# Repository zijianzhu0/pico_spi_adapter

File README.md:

# pico_spi_adapter
A rpi pico adapter for asm330lhh.

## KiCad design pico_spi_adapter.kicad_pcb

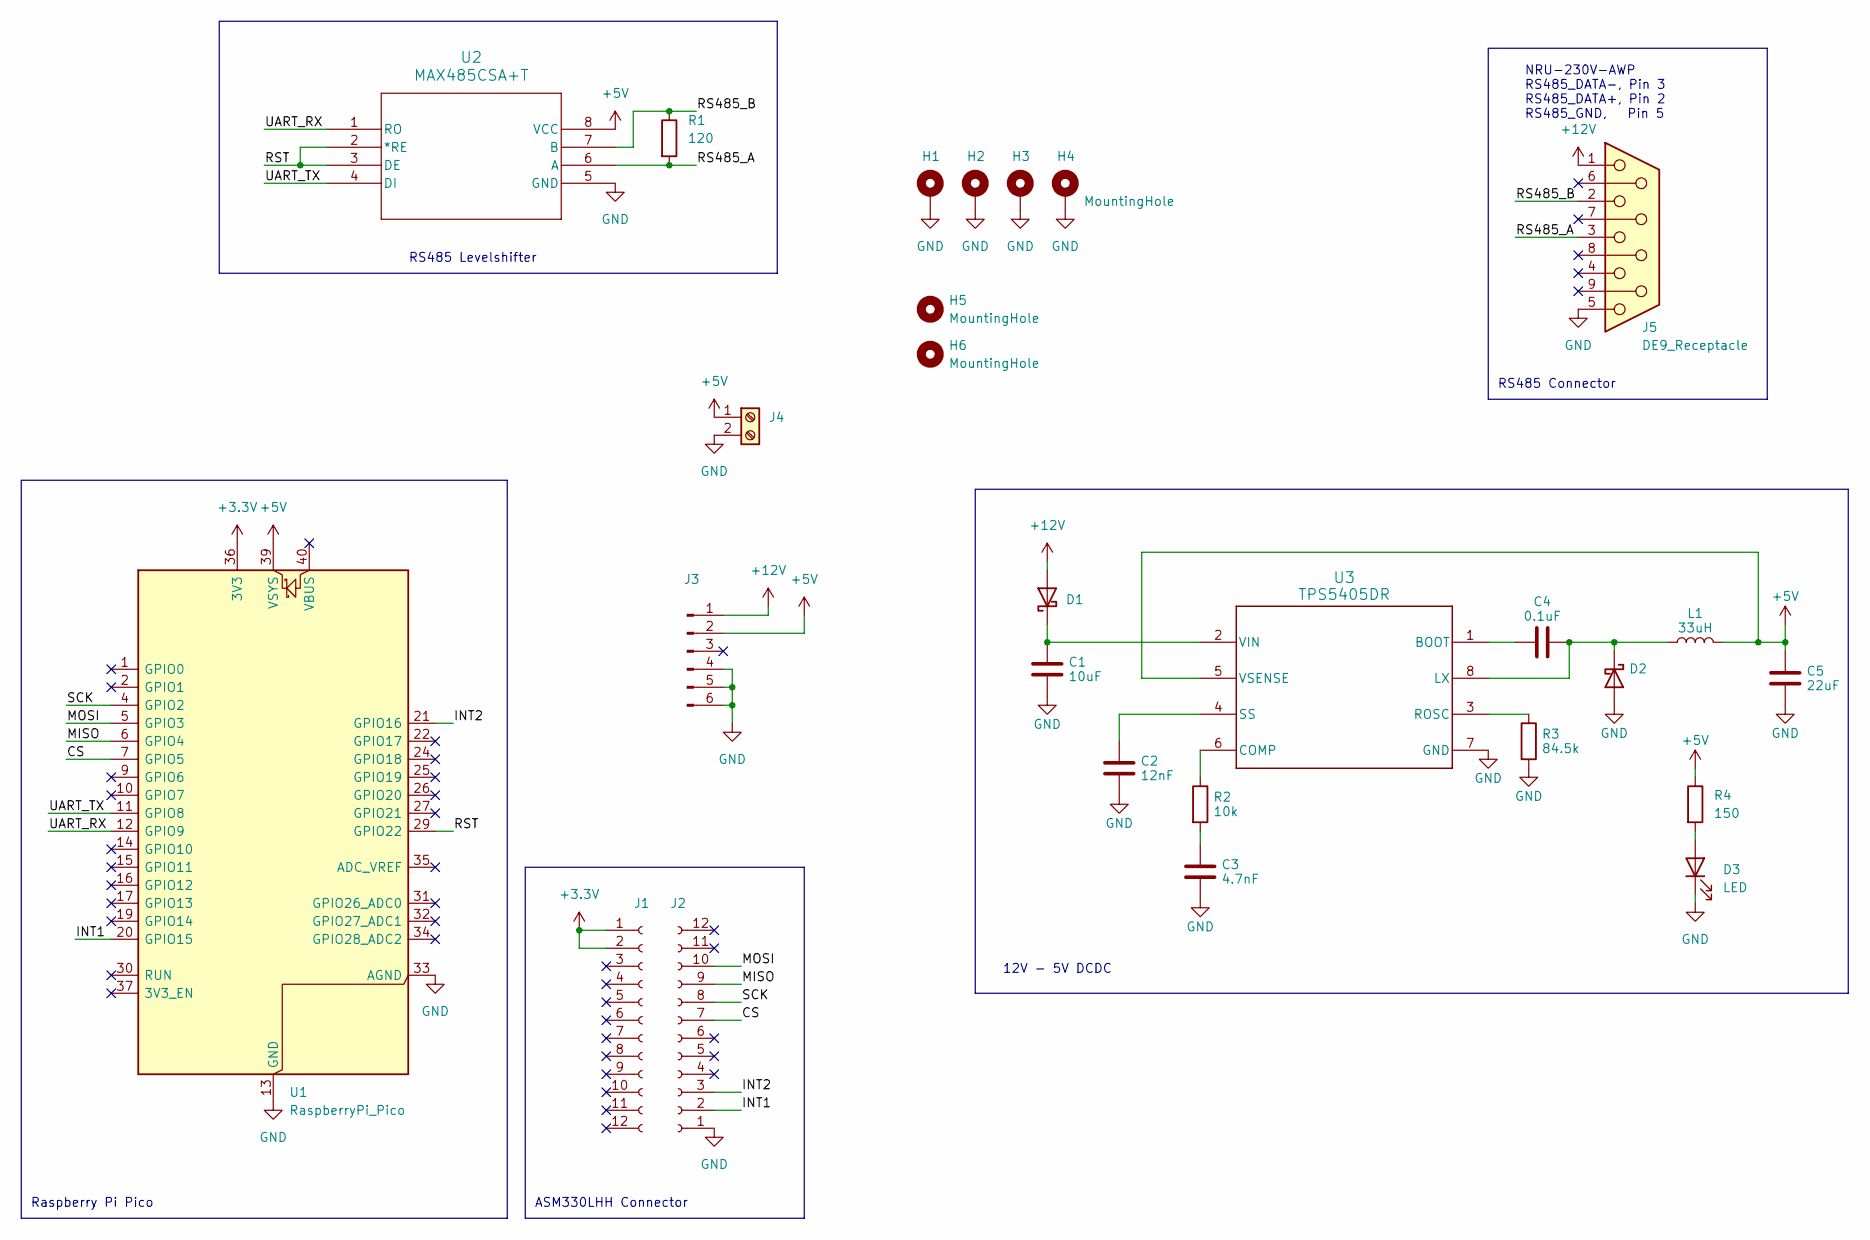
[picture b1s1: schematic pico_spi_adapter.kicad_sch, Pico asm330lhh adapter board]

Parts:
C1: 10uF; C_0805_2012Metric; JLCPCB Part# C15850
C2: 12nF; C_1206_3216Metric; JLCPCB Part# C710999
C3: 4.7nF; C_0805_2012Metric; JLCPCB Part# C50131
C4: 0.1uF; C_0805_2012Metric; JLCPCB Part# C1711
C5: 22uF; C_0805_2012Metric; JLCPCB Part# C5674
D1, D2: D_SMA; JLCPCB Part# C47460
D3: LED; LED_0201_0603Metric; JLCPCB Part# C2286
H1, H2, H3, H4: MountingHole; MountingHole_3.2mm_M3_DIN965_Pad
H5, H6: MountingHole; MountingHole_2.2mm_M2
J1, J2: Conn_01x12_Socket; PinSocket_1x12_P2.54mm_Vertical
J3: Conn_01x06_Pin; PinHeader_1x06_P2.54mm_Vertical
J4: Screw_Terminal_01x02; TerminalBlock_Phoenix_MPT-0,5-2-2.54_1x02_P2.54mm_Horizontal
J5: DE9_Receptacle; DSUB-9_Female_Horizontal_P2.77x2.84mm_EdgePinOffset14.56mm_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
L1: 33uH; L_Wuerth_HCM-7050; JLCPCB Part# C2847546
R1: 120; R_0805_2012Metric; JLCPCB PART# C17437
R2: 10k; R_0805_2012Metric; JLCPCB Part# C100047
R3: 84.5k; R_0805_2012Metric; JLCPCB Part# C17842
R4: 150; R_0805_2012Metric; JLCPCB Part# C96210
U1: RaspberryPi_Pico; RaspberryPi_Pico_Common
U2: MAX485CSA+T
U3: TPS5405DR; 21-0041-3-M_90-0096-8L_MXM

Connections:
+3.3V: J1.1, J1.2, U1.36 (3V3)
+5V: C5.2, J3.2, J4.1, L1.2, R4.1, U1.39 (VSYS), U2.8 (VCC), U3.5 (VSENSE)
+12V: D1.2 (A), J3.1, J5.1
/CS: J2.7, U1.7 (GPIO5)
/INT1: J2.2, U1.20 (GPIO15)
/INT2: J2.3, U1.21 (GPIO16)
/MISO: J2.9, U1.6 (GPIO4)
/MOSI: J2.10, U1.5 (GPIO3)
/RS485_A: J5.3, R1.2, U2.6 (A)
/RS485_B: J5.2, R1.1, U2.7 (B)
/RST: U1.29 (GPIO22), U2.2 (*RE), U2.3 (DE)
/SCK: J2.8, U1.4 (GPIO2)
/UART_RX: U1.12 (GPIO9), U2.1 (RO)
/UART_TX: U1.11 (GPIO8), U2.4 (DI)
GND: C1.2, C2.2, C3.2, C5.1, D2.2 (A), D3.1 (K), H1.1, H2.1, H3.1, H4.1, J2.1, J3.4, J3.5, J3.6, J4.2, J5.5, R3.2, U1.3 (GND), U1.8 (GND), U1.13 (GND), U1.18 (GND), U1.23 (GND), U1.28 (GND), U1.33 (AGND), U1.38 (GND), U2.5 (GND), U3.7 (GND)
unnamed: C3.1, R2.2
unnamed: C1.1, D1.1 (K), U3.2 (VIN)
unnamed: C4.2, D2.1 (K), L1.1, U3.8 (LX)
unnamed: D3.2 (A), R4.2
unnamed: C4.1, U3.1 (BOOT)
unnamed: R2.1, U3.6 (COMP)
unnamed: R3.1, U3.3 (ROSC)
unnamed: C2.1, U3.4 (SS)

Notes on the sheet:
RS485 Connector
ASM330LHH Connector
Raspberry Pi Pico
RS485 Levelshifter
NRU-230V-AWP RS485_DATA-, Pin 3 RS485_DATA+, Pin 2 RS485_GND, Pin 5
12V - 5V DCDC

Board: 2 copper layers, 25 parts (0 on the bottom side), 23 nets, no tracks yet.

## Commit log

2025-06-17 init commit
2025-06-17 added submodule
2025-06-19 checked out an older version to support kicad 7.0
2025-06-20 added components
2025-06-20 added docs
2025-07-08 added a few things
2025-07-11 added tps5405 docs
2025-07-11 added buck ic, updated layout
2025-07-11 added parts
2025-07-11 updated gitignore
2025-07-17 added calc & part selections.
2025-07-17 updated layouts
2025-07-17 layout size
2025-07-17 added a step file
2025-07-17 updated layout and mounting holes
